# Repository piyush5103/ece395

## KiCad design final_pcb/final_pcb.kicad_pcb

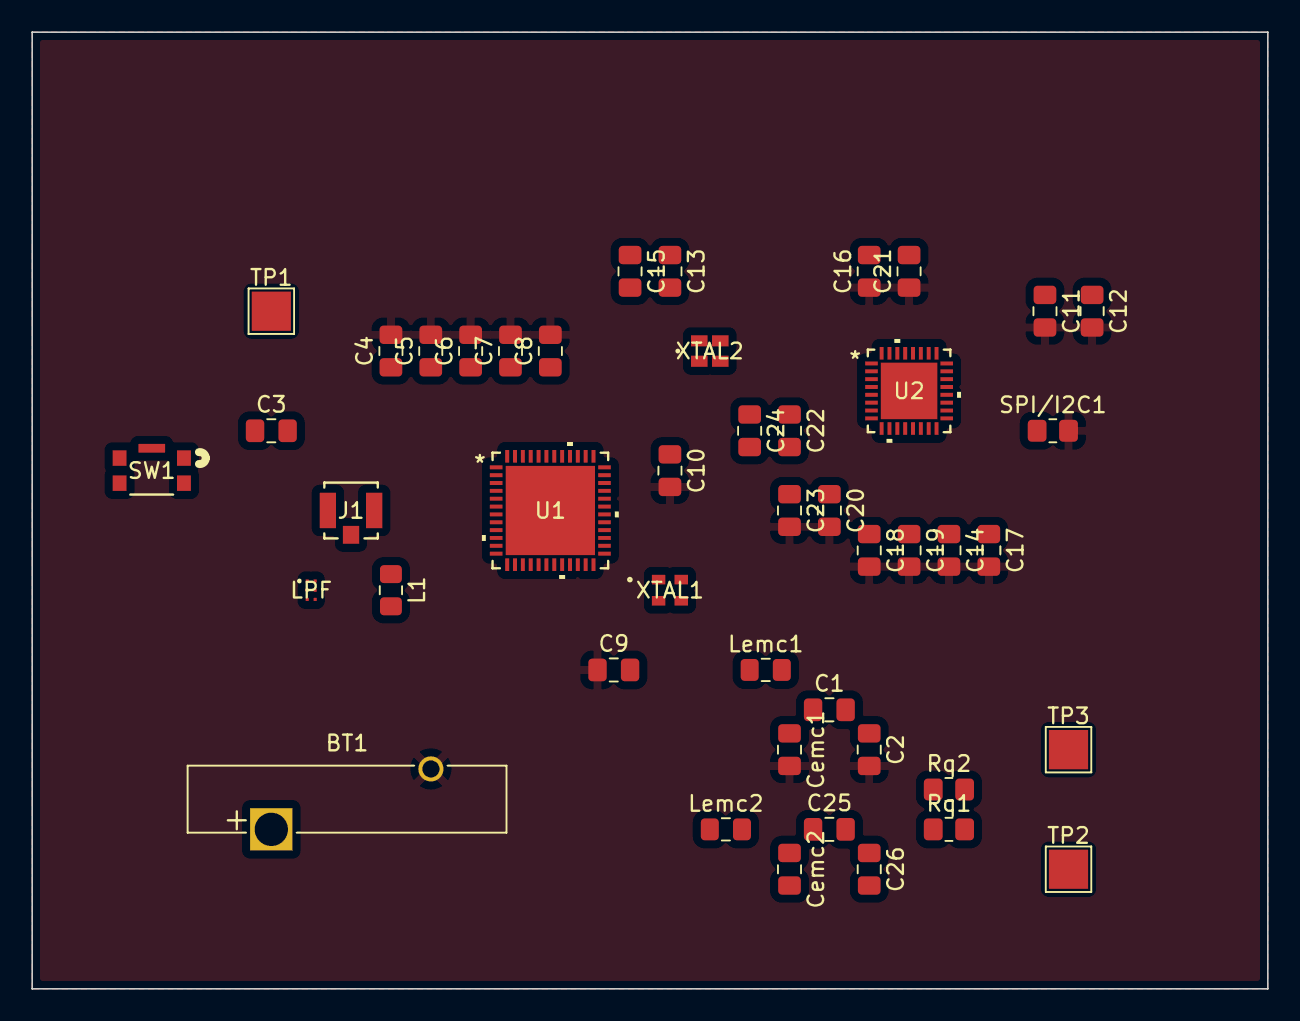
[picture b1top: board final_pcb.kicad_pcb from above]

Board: 2 copper layers, 78.7 x 61.0 mm, 45 parts (0 on the bottom side), 34 nets, no tracks yet.

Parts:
BT1: BHX1-1632-SM; Battery_Panasonic_CR2032-VS1N_Vertical_CircularHoles
C1, C25: 51pF; C_0805_2012Metric_Pad1.18x1.45mm_HandSolder
C2, C26: 198pF; C_0805_2012Metric_Pad1.18x1.45mm_HandSolder
C3: C; C_0805_2012Metric_Pad1.18x1.45mm_HandSolder
C4, C5, C6, C7, C8, C10, C11, C12, C13, C14, C15, C16, C17, C18, C19, C20, C21, C22, C23, C24: C_Small; C_0805_2012Metric_Pad1.18x1.45mm_HandSolder
C9: C_Polarized_Small_US; C_0805_2012Metric_Pad1.18x1.45mm_HandSolder
Cemc1, Cemc2: 180pF; C_0805_2012Metric_Pad1.18x1.45mm_HandSolder
J1: RECE.20279.001E.01; CON3_RECE.20279.001E.01_TAL
L1: 3.6nH; L_0805_2012Metric_Pad1.15x1.40mm_HandSolder
LPF: LPF; MLPF-WB55-01E3_STM
Lemc1, Lemc2: 560 nH; L_0805_2012Metric_Pad1.15x1.40mm_HandSolder
Rq1, Rq2: 0 Ohm; R_0805_2012Metric_Pad1.20x1.40mm_HandSolder
SPI/I2C1: R_Photo; R_0805_2012Metric_Pad1.20x1.40mm_HandSolder
SW1: KMR231GLFS; KMR2xxG_CNK
TP1, TP2, TP3: TestPoint; TestPoint_Pad_2.5x2.5mm
U1: STM32WB15CCU6; QFPN_15CCU6_STM
U2: ST25R3916B-AQWT; VFQFPN32_5X5_WETTABLE_STM
XTAL1: NX2016SA-32MHZ-EXS00A-CS11336; NX2016SA_NDK
XTAL2: XRCGB27M120F3M00R0; XTAL_XRCGB27M120F3M00R0_MUR

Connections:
+3V3: BT1.1, C4.1, C5.1, C6.1, C7.1, C8.1, C9.2, C10.1, C20.1, C23.1, U1.20 (VDD), U1.23 (VDDRF), U1.34 (VDDSMPS), U1.35 (VDD), U1.40 (VDD), U1.48 (VDD), U2.1 (VDD_IO), U2.8 (VDD), U2.10 (VDD_TX)
GND: BT1.2, C2.2, C4.2, C5.2, C6.2, C7.2, C8.2, C9.1, C10.2, C11.2, C12.2, C14.2, C16.1, C17.2, C18.2, C19.2, C20.2, C21.1, C23.2, Cemc1.2, SPI/I2C1.2, U1.22 (VSSRF), U1.32 (VSSSMPS), U2.21 (VSS)
GNDA: C22.2, C24.2, U2.26 (GND_A)
GNDD: C13.2, C15.2, U2.6 (GND_D)
GNDLPF: C3.2, J1.2 (GND), J1.3 (GND), LPF.2 (GND4), SW1.2, SW1.3, SW1.5, XTAL1.2, XTAL1.4
unnamed: C1.1, Cemc1.1, Lemc1.2
unnamed: C1.2, C2.1, Rq2.1
unnamed: C25.1, Cemc2.1, Lemc2.2
unnamed: C25.2, C26.1, Rq1.1
unnamed: C26.2, Cemc2.2
unnamed: J1.1 (SIGNAL), L1.1
unnamed: L1.2, LPF.1 (OUT)
unnamed: LPF.3 (IN), U1.21 (RF1)
unnamed: Rq1.2, TP2.1
unnamed: Rq2.2, TP3.1
unnamed: TP1.1, U1.1 (VBAT)
unnamed: C3.1, SW1.1, SW1.4, U1.7 (NRST)
unnamed: U1.13 (PA4), U2.29 (BSS)
unnamed: U1.14 (PA5), U2.30 (SCLK/SCL)
unnamed: U1.15 (PA6), U2.32 (MISO/SDA)
unnamed: U1.16 (PA7), U2.31 (MOSI)
unnamed: U1.24 (OSC_OUT), XTAL1.3
unnamed: U1.25 (OSC_IN), XTAL1.1
unnamed: U1.30 (PE4), U2.27 (IRQ)
unnamed: C13.1, C15.1, U2.3 (VDD_D)
unnamed: C16.2, U2.4 (XTO), XTAL2.1
unnamed: C21.2, U2.5 (XTI), XTAL2.3
unnamed: C22.1, C24.1, U2.7 (VDD_A)
unnamed: C14.1, C17.1, U2.11 (VDD_AM)
unnamed: Lemc1.1, U2.13 (RFO1)
unnamed: C18.1, C19.1, U2.9 (VDD_RF), U2.14 (VDD_DR)
unnamed: SPI/I2C1.1, U2.20 (I2C_EN)
unnamed: Lemc2.1, U2.22 (RFI1)
unnamed: C11.1, C12.1, U2.24 (AGDC)

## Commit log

2023-10-02 init
2023-10-02 added docs
2023-10-12 reorganized folders
2023-10-12 added ble custom with incorrect mcu
2023-10-12 missing files
2023-10-24 added foldder oct 24
2023-11-07 pcb files
2023-12-14 Add files via upload
    Done!
